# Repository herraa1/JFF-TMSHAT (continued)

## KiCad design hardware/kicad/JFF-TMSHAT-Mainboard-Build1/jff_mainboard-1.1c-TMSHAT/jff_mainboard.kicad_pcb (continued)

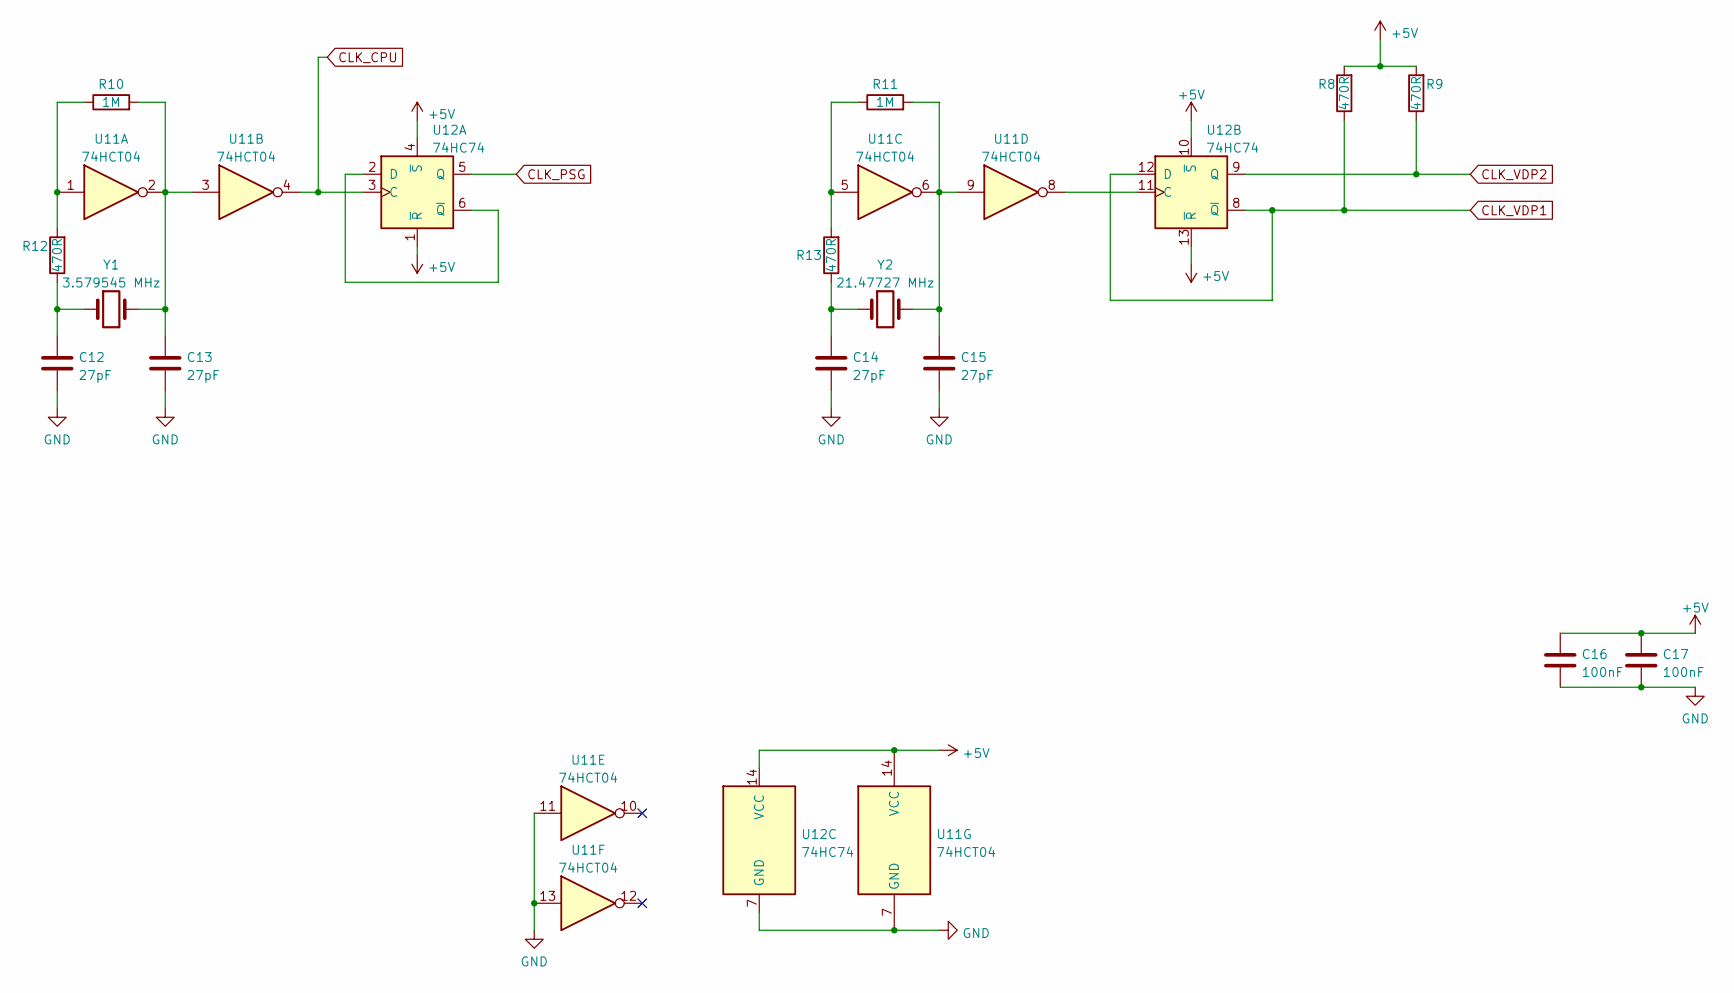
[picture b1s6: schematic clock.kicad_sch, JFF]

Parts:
C12, C13, C14, C15: 27pF; C_Disc_D3.0mm_W2.0mm_P2.50mm
C16, C17: 100nF; C_Disc_D3.0mm_W2.0mm_P2.50mm
R8, R9, R12, R13: 470R; R_Axial_DIN0204_L3.6mm_D1.6mm_P7.62mm_Horizontal
R10, R11: 1M; R_Axial_DIN0204_L3.6mm_D1.6mm_P7.62mm_Horizontal
U11: 74HCT04; DIP-14_W7.62mm_Socket
U12: 74HC74; DIP-14_W7.62mm_Socket
Y1: 3.579545 MHz; Crystal_HC49-U_Vertical
Y2: 21.47727 MHz; Crystal_HC49-U_Vertical

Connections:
+5V: C16.1, C17.1, R8.2, R9.2, U11.14 (VCC), U12.1 (~R), U12.4 (~S), U12.10 (~S), U12.13 (~R), U12.14 (VCC); also elsewhere on the board
CLK_CPU: U11.4, U12.3 (C); also elsewhere on the board
CLK_PSG: U12.5 (Q); also elsewhere on the board
CLK_VDP1: R8.1, U12.8 (~Q), U12.12 (D); also elsewhere on the board
CLK_VDP2: R9.1, U12.9 (Q); also elsewhere on the board
GND: C12.2, C13.2, C14.2, C15.2, C16.2, C17.2, U11.7 (GND), U11.11, U11.13, U12.7 (GND); also elsewhere on the board
unnamed: C12.1, R12.1, Y1.1
unnamed: C13.1, R10.2, U11.2, U11.3, Y1.2
unnamed: C14.1, R13.1, Y2.1
unnamed: C15.1, R11.2, U11.6, U11.9, Y2.2
unnamed: R10.1, R12.2, U11.1
unnamed: R11.1, R13.2, U11.5
unnamed: U12.2 (D), U12.6 (~Q)
unnamed: U11.8, U12.11 (C)

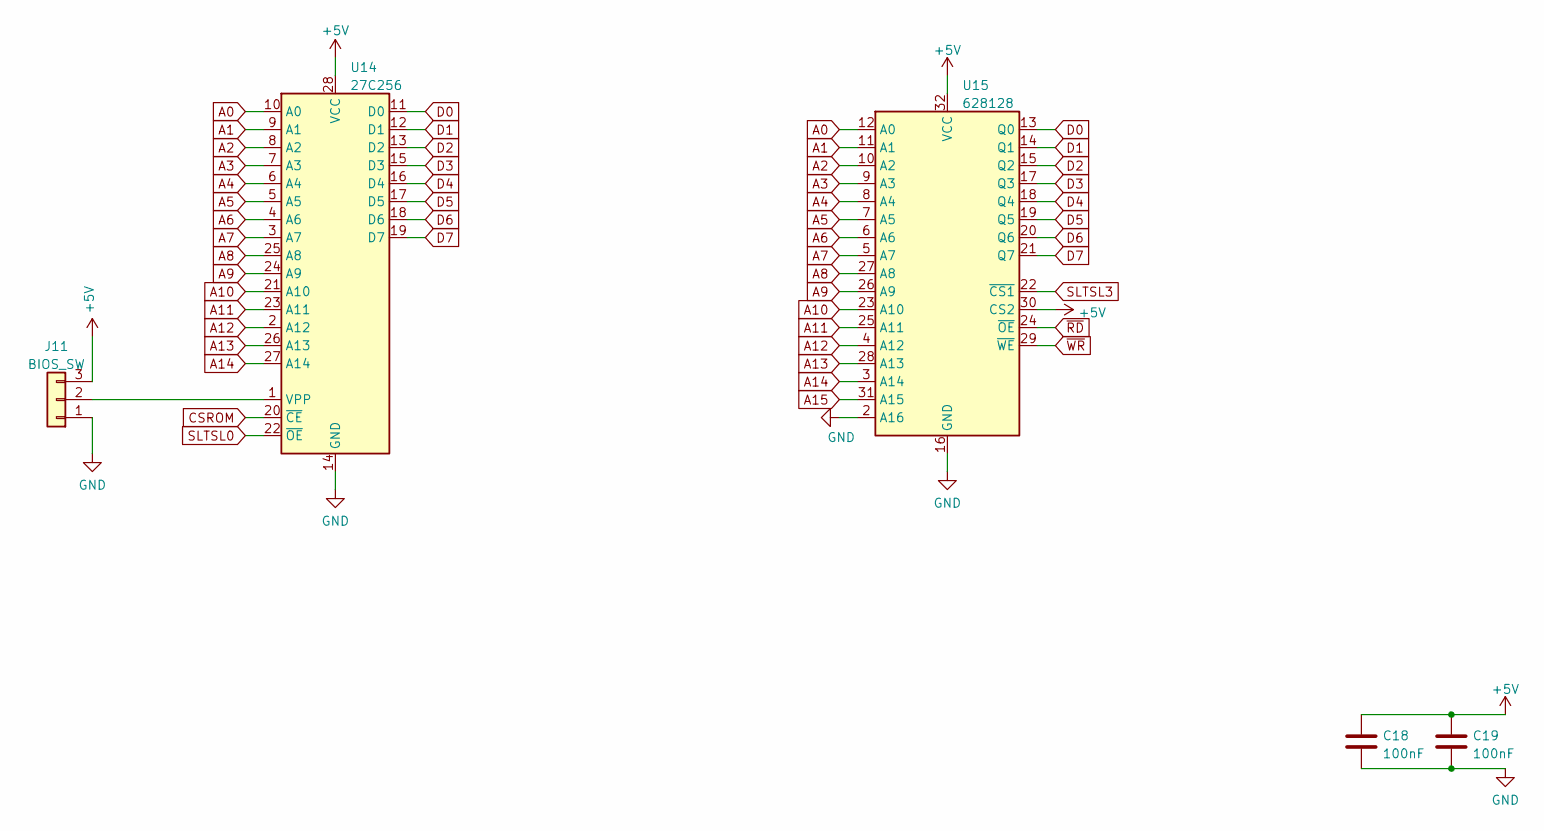
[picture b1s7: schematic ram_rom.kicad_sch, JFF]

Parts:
C18, C19: 100nF; C_Disc_D3.0mm_W2.0mm_P2.50mm
J11: BIOS_SW; PinHeader_1x03_P2.54mm_Vertical
U14: 27C256; DIP-28_W15.24mm_Socket
U15: 628128; DIP-32_W15.24mm_Socket

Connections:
+5V: C18.1, C19.1, J11.3, U14.28 (VCC), U15.30 (CS2), U15.32 (VCC); also elsewhere on the board
A0: U14.10 (A0), U15.12 (A0); also elsewhere on the board
A1: U14.9 (A1), U15.11 (A1); also elsewhere on the board
A2: U14.8 (A2), U15.10 (A2); also elsewhere on the board
A3: U14.7 (A3), U15.9 (A3); also elsewhere on the board
A4: U14.6 (A4), U15.8 (A4); also elsewhere on the board
A5: U14.5 (A5), U15.7 (A5); also elsewhere on the board
A6: U14.4 (A6), U15.6 (A6); also elsewhere on the board
A7: U14.3 (A7), U15.5 (A7); also elsewhere on the board
A8: U14.25 (A8), U15.27 (A8); also elsewhere on the board
A9: U14.24 (A9), U15.26 (A9); also elsewhere on the board
A10: U14.21 (A10), U15.23 (A10); also elsewhere on the board
A11: U14.23 (A11), U15.25 (A11); also elsewhere on the board
A12: U14.2 (A12), U15.4 (A12); also elsewhere on the board
A13: U14.26 (A13), U15.28 (A13); also elsewhere on the board
A14: U14.27 (A14), U15.3 (A14); also elsewhere on the board
A15: U15.31 (A15); also elsewhere on the board
CSROM: U14.20 (~CE); also elsewhere on the board
D0: U14.11 (D0), U15.13 (Q0); also elsewhere on the board
D1: U14.12 (D1), U15.14 (Q1); also elsewhere on the board
D2: U14.13 (D2), U15.15 (Q2); also elsewhere on the board
D3: U14.15 (D3), U15.17 (Q3); also elsewhere on the board
D4: U14.16 (D4), U15.18 (Q4); also elsewhere on the board
D5: U14.17 (D5), U15.19 (Q5); also elsewhere on the board
D6: U14.18 (D6), U15.20 (Q6); also elsewhere on the board
D7: U14.19 (D7), U15.21 (Q7); also elsewhere on the board
GND: C18.2, C19.2, J11.1, U14.14 (GND), U15.2 (A16), U15.16 (GND); also elsewhere on the board
unnamed: J11.2, U14.1 (VPP)
SLTSL0: U14.22 (~OE); also elsewhere on the board
SLTSL3: U15.22 (~CS1); also elsewhere on the board
~RD: U15.24 (~OE); also elsewhere on the board
~WR: U15.29 (~WE); also elsewhere on the board

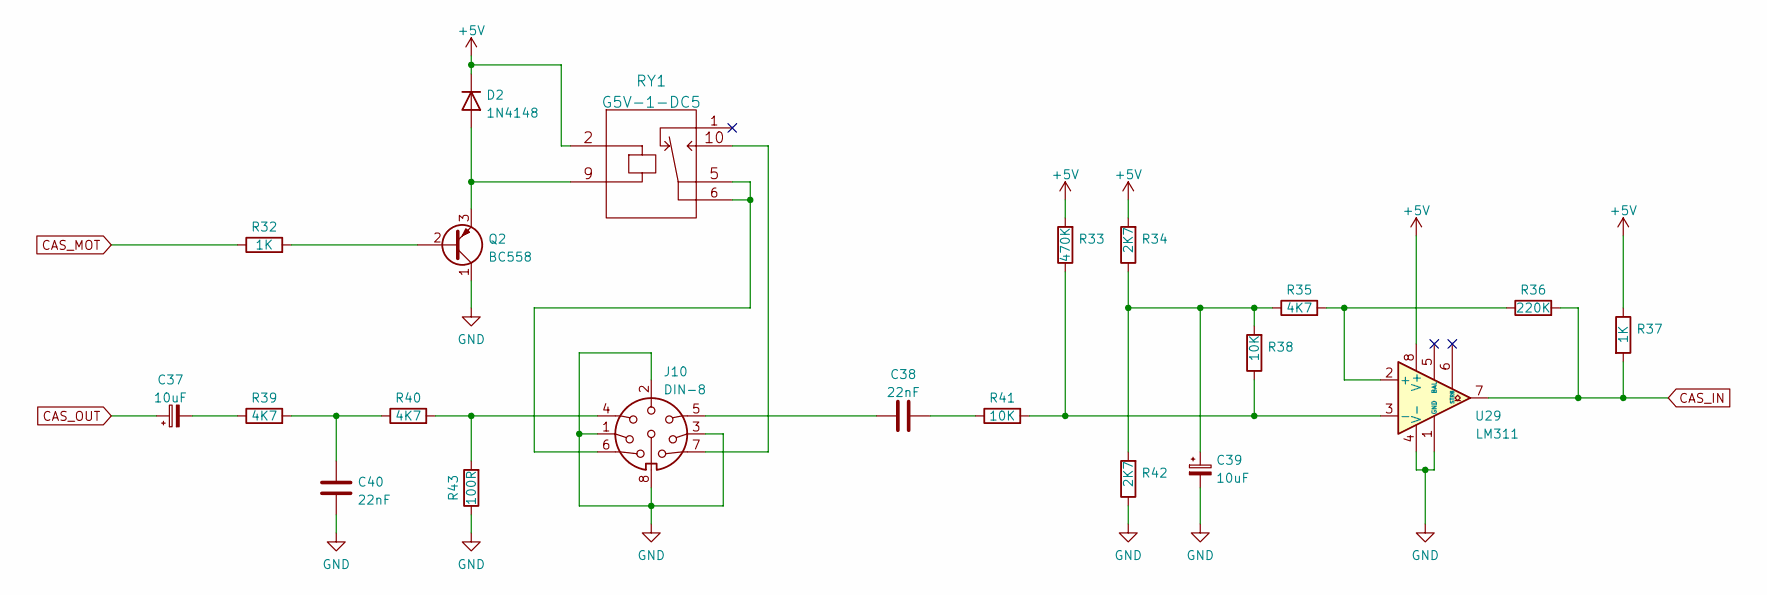
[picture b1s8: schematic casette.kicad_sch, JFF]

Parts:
C37, C39: 10uF; CP_Radial_D5.0mm_P2.50mm
C38, C40: 22nF; C_Disc_D3.0mm_W2.0mm_P2.50mm
D2: 1N4148; D_DO-35_SOD27_P7.62mm_Horizontal
J10: DIN-8; DIN8_eu
Q2: BC558; TO-92_Inline
R32, R37: 1K; R_Axial_DIN0204_L3.6mm_D1.6mm_P7.62mm_Horizontal
R33: 470K; R_Axial_DIN0204_L3.6mm_D1.6mm_P7.62mm_Horizontal
R34, R42: 2K7; R_Axial_DIN0204_L3.6mm_D1.6mm_P7.62mm_Horizontal
R35, R39, R40: 4K7; R_Axial_DIN0204_L3.6mm_D1.6mm_P7.62mm_Horizontal
R36: 220K; R_Axial_DIN0204_L3.6mm_D1.6mm_P7.62mm_Horizontal
R38, R41: 10K; R_Axial_DIN0204_L3.6mm_D1.6mm_P7.62mm_Horizontal
R43: 100R; R_Axial_DIN0204_L3.6mm_D1.6mm_P7.62mm_Horizontal
RY1: G5V-1-DC5; Relay_SPDT
U29: LM311; DIP-8_W7.62mm_Socket

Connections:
+5V: D2.1 (K), R33.2, R34.2, R37.1, RY1.2, U29.8 (V+); also elsewhere on the board
CAS_IN: R36.2, R37.2, U29.7; also elsewhere on the board
CAS_MOT: R32.1; also elsewhere on the board
CAS_OUT: C37.1; also elsewhere on the board
GND: C39.2, C40.1, J10.1, J10.2, J10.3, J10.8, Q2.1 (C), R42.1, R43.1, U29.1 (GND), U29.4 (V-); also elsewhere on the board
unnamed: C37.2, R39.1
unnamed: C38.1, J10.5
unnamed: C38.2, R41.1
unnamed: C39.1, R34.1, R35.1, R38.2, R42.2
unnamed: C40.2, R39.2, R40.1
unnamed: D2.2 (A), Q2.3 (E), RY1.9
unnamed: J10.4, R40.2, R43.2
unnamed: J10.6, RY1.5, RY1.6
unnamed: J10.7, RY1.10
unnamed: Q2.2 (B), R32.2
unnamed: R35.2, R36.1, U29.2 (+)
unnamed: R33.1, R38.1, R41.2, U29.3 (-)

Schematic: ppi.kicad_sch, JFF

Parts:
C29, C30, C31, C32, C33, C34, C35, C36: 100nF; C_Disc_D3.0mm_W2.0mm_P2.50mm
J9: KEYBOARD; PinHeader_2x08_P2.54mm_Vertical
R2: 10K; R_Axial_DIN0204_L3.6mm_D1.6mm_P7.62mm_Horizontal
RN1: 4.7K; R_Array_SIP9
U16: 74LS02; DIP-14_W7.62mm_Socket
U21: 74LS00; DIP-14_W7.62mm_Socket
U22: 74LS139; DIP-16_W7.62mm_Socket
U23: 74LS153; DIP-16_W7.62mm_Socket
U24: 74LS32; DIP-14_W7.62mm_Socket
U26: 82C55A; DIP-40_W15.24mm_Socket
U27: 74LS08; DIP-14_W7.62mm_Socket
U28: 74LS138; DIP-16_W7.62mm_Socket

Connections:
+5V: C29.1, C30.1, C31.1, C32.1, C33.1, C34.1, C35.1, C36.1, J9.2, R2.1, RN1.1 (common), U21.14 (VCC), U22.16 (VCC), U23.16 (VCC), U24.14 (VCC), U26.26 (VCC), U27.14 (VCC), U28.16 (VCC); also elsewhere on the board
A0: U26.9 (A0); also elsewhere on the board
A1: U26.8 (A1); also elsewhere on the board
A3: U28.1 (A0); also elsewhere on the board
A4: U28.2 (A1); also elsewhere on the board
A5: U28.3 (A2); also elsewhere on the board
A6: U28.5 (E2); also elsewhere on the board
A7: U28.6 (E3); also elsewhere on the board
A14: U22.14 (A0), U23.14 (S0); also elsewhere on the board
A15: U22.13 (A1), U23.2 (S1); also elsewhere on the board
BEEP: U26.10 (PC7); also elsewhere on the board
CAS_MOT: U26.13 (PC4); also elsewhere on the board
CAS_OUT: U26.12 (PC5); also elsewhere on the board
CS1: U24.6, U27.2, U27.4; also elsewhere on the board
CS2: U24.8, U27.5; also elsewhere on the board
CS12: U27.6; also elsewhere on the board
CSROM: U27.3; also elsewhere on the board
CS_PPI: U21.1, U26.6 (~CS), U28.10 (O5)
CS_PSG: U28.11 (O4); also elsewhere on the board
CS_VDP: U28.12 (O3); also elsewhere on the board
D0: U26.34 (D0); also elsewhere on the board
D1: U26.33 (D1); also elsewhere on the board
D2: U26.32 (D2); also elsewhere on the board
D3: U26.31 (D3); also elsewhere on the board
D4: U26.30 (D4); also elsewhere on the board
D5: U26.29 (D5); also elsewhere on the board
D6: U26.28 (D6); also elsewhere on the board
D7: U26.27 (D7); also elsewhere on the board
GND: C29.2, C30.2, C31.2, C32.2, C33.2, C34.2, C35.2, C36.2, J9.16, U16.9, U21.7 (GND), U21.9, U21.10, U21.12, U21.13, U22.8 (GND), U23.8 (GND), U24.7 (GND), U24.12, U24.13, U26.7 (GND), U27.7 (GND), U27.12, U27.13, U28.8 (GND); also elsewhere on the board
unnamed: U16.10, U24.2
unnamed: U21.3, U21.4
unnamed: U22.2 (A0), U23.7 (Za)
unnamed: U22.3 (A1), U23.9 (Zb)
unnamed: U22.1 (E), U24.3
unnamed: U22.12 (O0), U27.1
unnamed: U22.11 (O1), U24.5
unnamed: U22.10 (O2), U24.10
unnamed: U21.2, U21.6, U23.1 (Ea), U23.15 (Eb)
PA0: U23.6 (I0a), U26.4 (PA0)
PA1: U23.10 (I0b), U26.3 (PA1)
PA2: U23.5 (I1a), U26.2 (PA2)
PA3: U23.11 (I1b), U26.1 (PA3)
PA4: U23.4 (I2a), U26.40 (PA4)
PA5: U23.12 (I2b), U26.39 (PA5)
PA6: U23.3 (I3a), U26.38 (PA6)
PA7: U23.13 (I3b), U26.37 (PA7)
PB0: J9.1, RN1.2 (R1), U26.18 (PB0)
PB1: J9.3, RN1.3 (R2), U26.19 (PB1)
PB2: J9.5, RN1.4 (R3), U26.20 (PB2)
PB3: J9.7, RN1.5 (R4), U26.21 (PB3)
PB4: J9.9, RN1.6 (R5), U26.22 (PB4)
PB5: J9.11, RN1.7 (R6), U26.23 (PB5)
PB6: J9.13, RN1.8 (R7), U26.24 (PB6)
PB7: J9.15, RN1.9 (R8), U26.25 (PB7)
PC0: J9.4, U26.14 (PC0)
PC1: J9.6, U26.15 (PC1)
PC2: J9.8, U26.16 (PC2)
PC3: J9.10, U26.17 (PC3)
PC6: J9.12, U26.11 (PC6)
RESET: U26.35 (RESET); also elsewhere on the board
SLTSL0: U22.4 (O0); also elsewhere on the board
SLTSL1: U22.5 (O1); also elsewhere on the board
SLTSL2: U22.6 (O2); also elsewhere on the board
SLTSL3: U22.7 (O3); also elsewhere on the board
~INT: U27.8; also elsewhere on the board
~IORQ: U28.4 (E1); also elsewhere on the board
~MREQ: U24.1; also elsewhere on the board
~RD: U22.15 (E), U24.4, U24.9, U26.5 (~RD); also elsewhere on the board
~RESET: U21.5; also elsewhere on the board
~RFSH: U16.8; also elsewhere on the board
~SLT_INT: R2.2, U27.10; also elsewhere on the board
~VDP_INT: U27.9; also elsewhere on the board
~WR: U26.36 (~WR); also elsewhere on the board

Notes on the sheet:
IO90 - PRINTER (NOT USED) IO98 - VDP IOA0 - PSG IOA8 - PPI

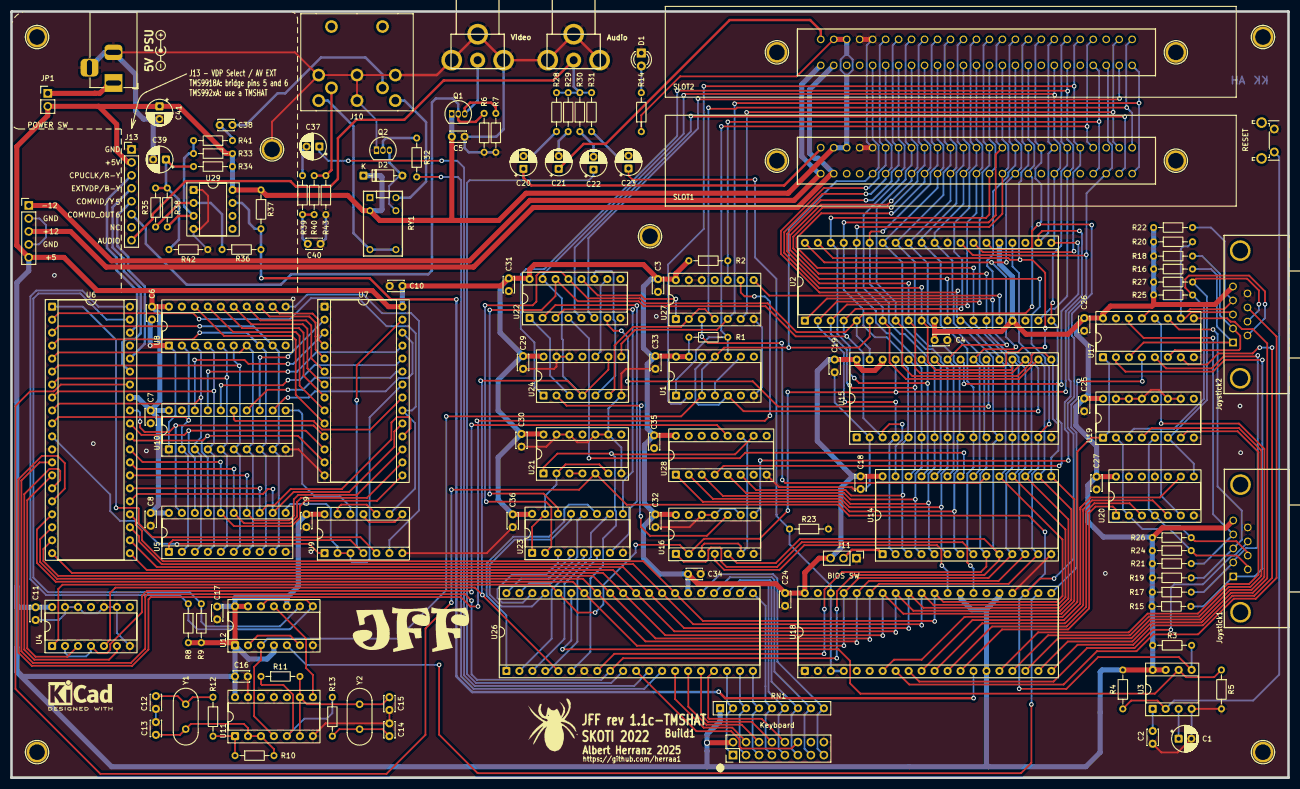
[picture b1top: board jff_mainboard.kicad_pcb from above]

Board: 2 copper layers, 250.0 x 150.0 mm, 144 parts (0 on the bottom side), 198 nets.

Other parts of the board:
G01: LOGO; jff_logo_25x10
G02: LOGO; spider_logo_small_neg
MH01, MH02, MH03, MH04, MH05, MH06, MH07, MH08, MH09, MH10: VAL*; Hole_3mm

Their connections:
GND: MH01.1, MH02.1, MH03.1, MH04.1, MH05.1, MH06.1, MH07.1, MH08.1, MH09.1, MH10.1; also elsewhere on the board

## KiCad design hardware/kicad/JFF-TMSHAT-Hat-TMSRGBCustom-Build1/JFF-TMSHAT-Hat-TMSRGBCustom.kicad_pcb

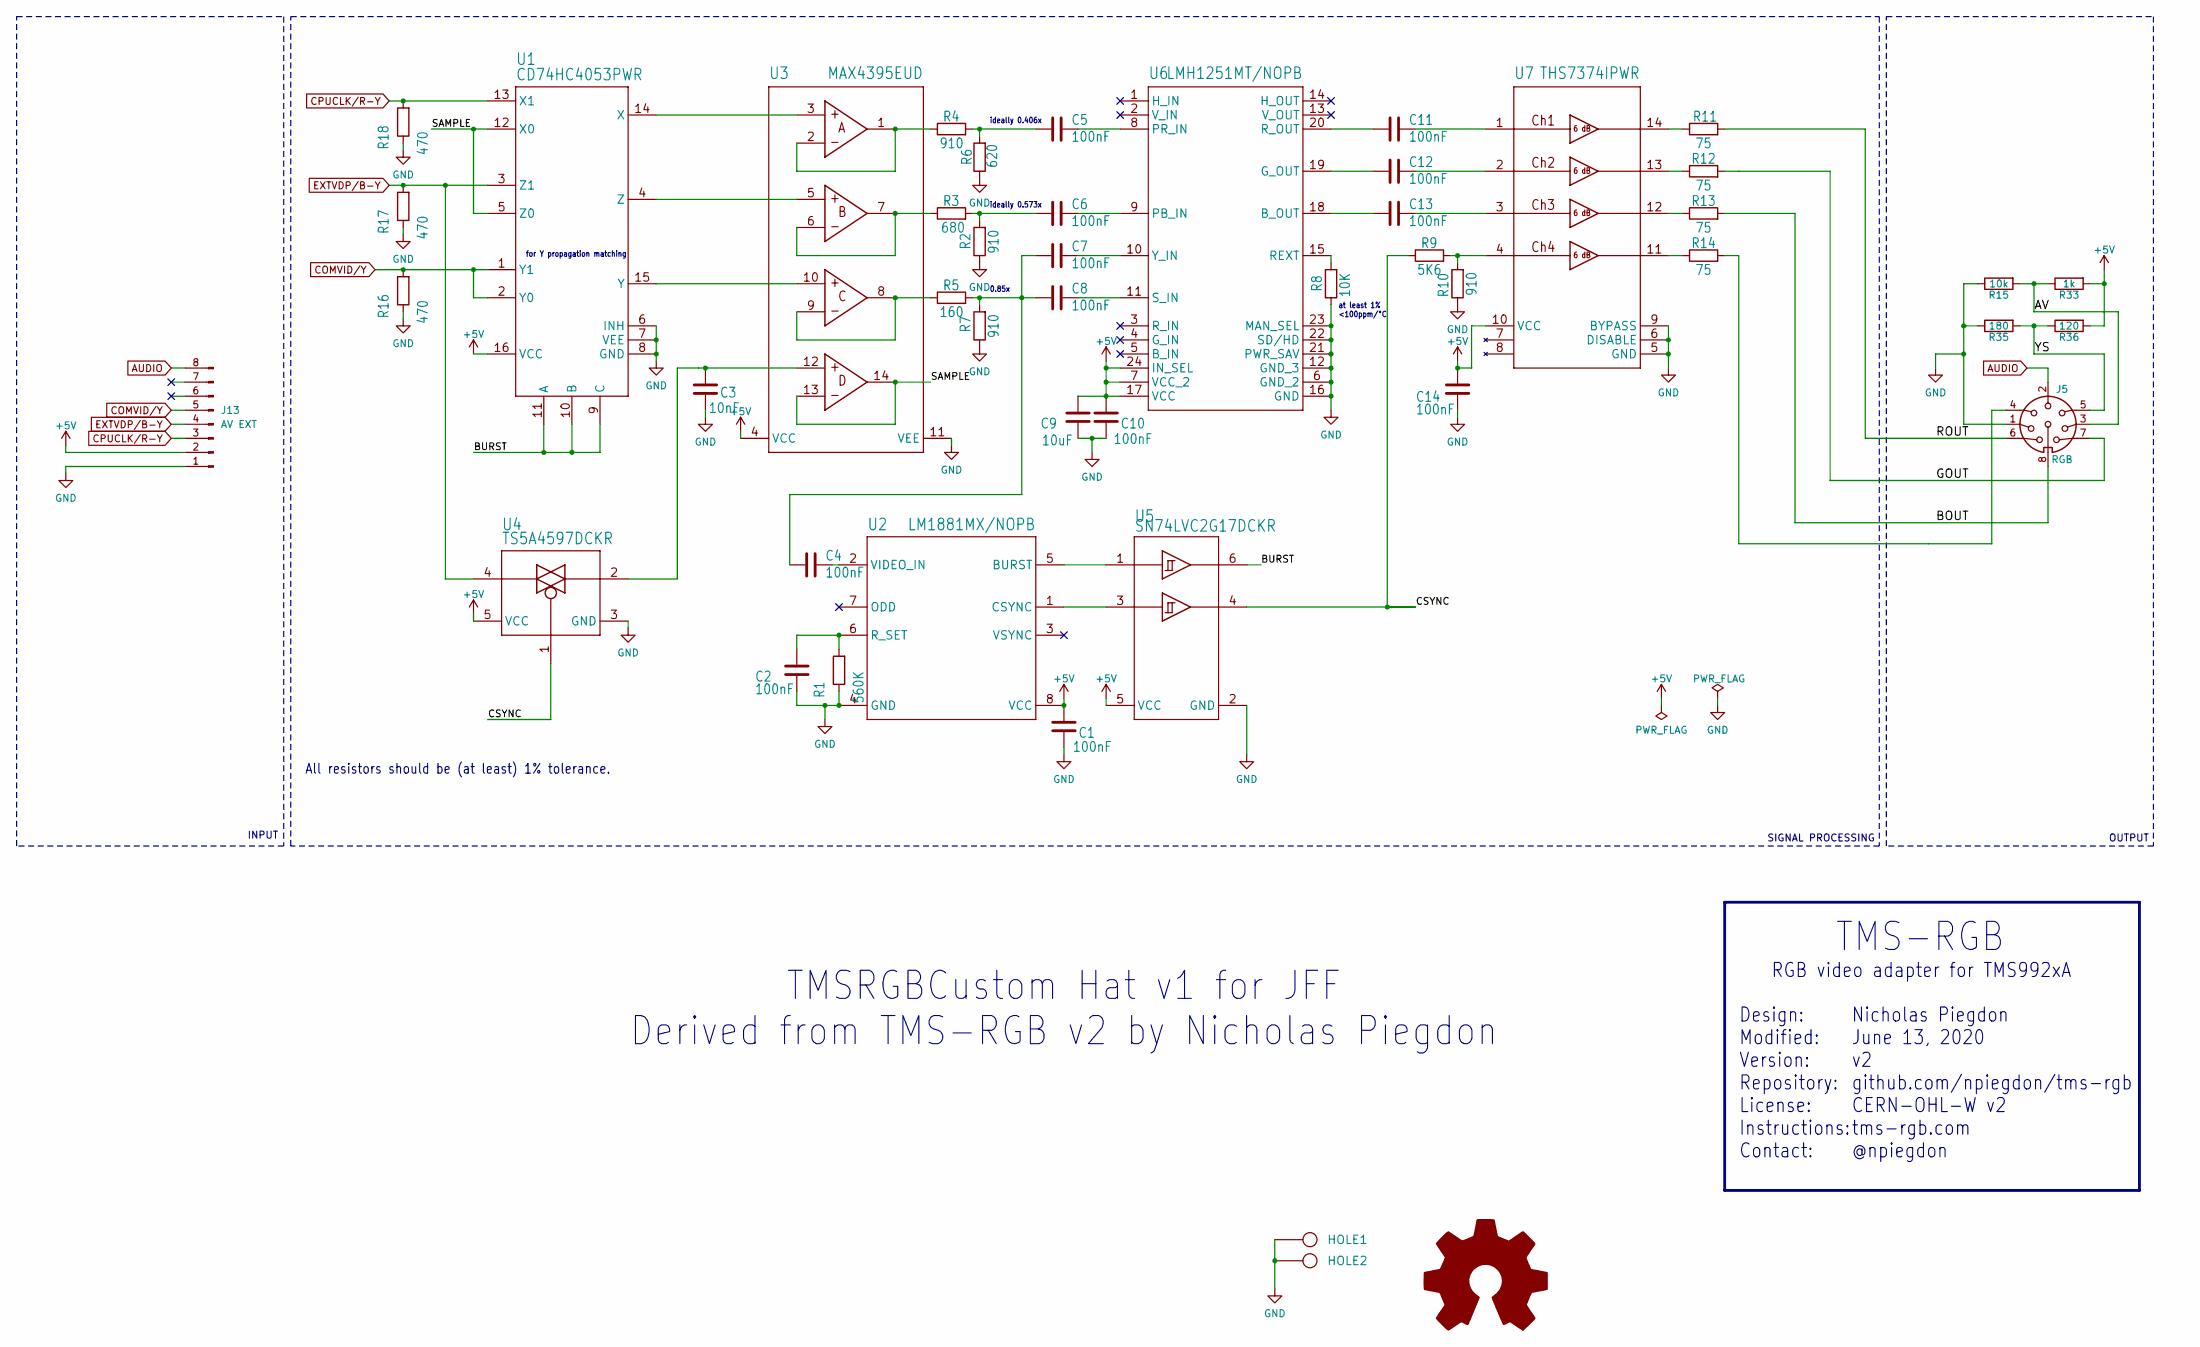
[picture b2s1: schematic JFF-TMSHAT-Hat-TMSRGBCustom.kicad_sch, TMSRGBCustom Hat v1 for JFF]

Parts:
C1, C2, C4, C5, C6, C7, C8, C10, C11, C12, C13, C14: 100nF; C_0805_2012Metric_Pad1.18x1.45mm_HandSolder
C3: 10nF; C_0805_2012Metric_Pad1.18x1.45mm_HandSolder
C9: 10uF; C_1206_3216Metric_Pad1.33x1.80mm_HandSolder
HOLE1, HOLE2: HOLE; Hole_3mm
J5: RGB; DIN8_eu
J13: AV EXT; PinSocket_1x08_P2.54mm_Vertical
R1: 560K; R_0805_2012Metric_Pad1.20x1.40mm_HandSolder
R2, R4, R7, R10: 910; R_0805_2012Metric_Pad1.20x1.40mm_HandSolder
R3: 680; R_0805_2012Metric_Pad1.20x1.40mm_HandSolder
R5: 160; R_0805_2012Metric_Pad1.20x1.40mm_HandSolder
R6: 620; R_0805_2012Metric_Pad1.20x1.40mm_HandSolder
R8: 10K; R_0805_2012Metric_Pad1.20x1.40mm_HandSolder
R9: 5K6; R_0805_2012Metric_Pad1.20x1.40mm_HandSolder
R11, R12, R13, R14: 75; R_0805_2012Metric_Pad1.20x1.40mm_HandSolder
R15: 10k; R_0805_2012Metric_Pad1.20x1.40mm_HandSolder
R16, R17, R18: 470; R_0805_2012Metric_Pad1.20x1.40mm_HandSolder
R33: 1k; R_0805_2012Metric_Pad1.20x1.40mm_HandSolder
R35: 180; R_0805_2012Metric_Pad1.20x1.40mm_HandSolder
R36: 120; R_0805_2012Metric_Pad1.20x1.40mm_HandSolder
SYM1: Logo_Open_Hardware_Large; OSHW-Logo_7.5x8mm_SilkScreen
U1: CD74HC4053PWR; TSSOP-16_4.4x5mm_P0.65mm
U2: LM1881MX/NOPB; SOIC-8_3.9x4.9mm_P1.27mm
U3: MAX4395EUD; TSSOP-14_4.4x5mm_P0.65mm
U4: TS5A4597DCKR; SOT-353_SC-70-5_Handsoldering
U5: SN74LVC2G17DCKR; SOT-363_SC-70-6_Handsoldering
U6: LMH1251MT/NOPB; TSSOP-24_4.4x7.8mm_P0.65mm
U7: THS7374IPWR; TSSOP-14_4.4x5mm_P0.65mm

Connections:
+5V: C1.1, C9.1, C10.1, C14.1, J13.2, R33.2, R36.2, U1.16 (VCC), U2.8 (VCC), U3.4 (VCC), U4.5 (VCC), U5.5 (VCC), U6.7 (VCC_2), U6.17 (VCC), U6.24 (IN_SEL), U7.10 (VCC)
/AV: J5.3, R15.2, R33.1
/BOUT: J5.8, R13.2
/BURST: U1.9 (C), U1.10 (B), U1.11 (A), U5.6 (1Y)
/CSYNC: R9.1, U4.1 (IN), U5.4 (2Y)
/GOUT: J5.7, R12.2
/ROUT: J5.6, R11.2
/SAMPLE: U1.5 (Z0), U1.12 (X0), U3.13 (D-), U3.14 (D)
/YS: J5.5, R35.2, R36.1
AUDIO: J5.2, J13.8
COMVID/Y: J13.5, R16.2, U1.1 (Y1), U1.2 (Y0)
CPUCLK/R-Y: J13.3, R18.2, U1.13 (X1)
EXTVDP/B-Y: J13.4, R17.2, U1.3 (Z1), U4.4 (NC)
GND: C1.2, C2.2, C3.2, C9.2, C10.2, C14.2, HOLE1.1, HOLE2.1, J5.1, J13.1, R1.1, R2.1, R6.1, R7.1, R8.1, R10.1, R15.1, R16.1, R17.1, R18.1, R35.1, U1.6 (INH), U1.7 (VEE), U1.8 (GND), U2.4 (GND), U3.11 (VEE), U4.3 (GND), U5.2 (GND), U6.6 (GND_2), U6.12 (GND_3), U6.16 (GND), U6.21 (PWR_SAV), U6.22 (SD/HD), U6.23 (MAN_SEL), U7.5 (GND), U7.6 (DISABLE), U7.9 (BYPASS)
unnamed: C4.1, C7.1, C8.1, R5.2, R7.2
unnamed: C5.1, R4.2, R6.2
unnamed: C6.1, R2.2, R3.2
unnamed: J5.4, R14.2
unnamed: U1.14 (X), U3.3 (A+)
unnamed: U1.15 (Y), U3.10 (C+)
unnamed: U1.4 (Z), U3.5 (B+)
unnamed: U2.5 (BURST), U5.1 (1A)
unnamed: U2.1 (CSYNC), U5.3 (2A)
unnamed: C2.1, R1.2, U2.6 (R_SET)
unnamed: C4.2, U2.2 (VIDEO_IN)
unnamed: R4.1, U3.1 (A), U3.2 (A-)
unnamed: R3.1, U3.6 (B-), U3.7 (B)
unnamed: R5.1, U3.8 (C), U3.9 (C-)
unnamed: C3.1, U3.12 (D+), U4.2 (COM)
unnamed: C13.1, U6.18 (B_OUT)
unnamed: C12.1, U6.19 (G_OUT)
unnamed: C6.2, U6.9 (PB_IN)
unnamed: C5.2, U6.8 (PR_IN)
unnamed: R8.2, U6.15 (REXT)
unnamed: C11.1, U6.20 (R_OUT)
unnamed: C8.2, U6.11 (S_IN)
unnamed: C7.2, U6.10 (Y_IN)
unnamed: C11.2, U7.1 (CH1IN)
unnamed: R11.1, U7.14 (CH1OUT)
unnamed: C12.2, U7.2 (CH2IN)
unnamed: R12.1, U7.13 (CH2OUT)
unnamed: C13.2, U7.3 (CH3IN)
unnamed: R13.1, U7.12 (CH3OUT)
unnamed: R9.2, R10.2, U7.4 (CH4IN)
unnamed: R14.1, U7.11 (CH4OUT)

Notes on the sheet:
for Y propagation matching
${TITLE} Derived from TMS-RGB v2 by Nicholas Piegdon
OUTPUT
at least 1% <100ppm/°C
TMS-RGB
ideally 0.573x
SIGNAL PROCESSING
Nicholas Piegdon June 13, 2020 v2 github.com/npiegdon/tms-rgb CERN-OHL-W v2 tms-rgb.com @npiegdon
All resistors should be (at least) 1% tolerance.
RGB video adapter for TMS992xA
Design: Modified: Version: Repository: License: Instructions: Contact:
0.85x
ideally 0.406x
INPUT

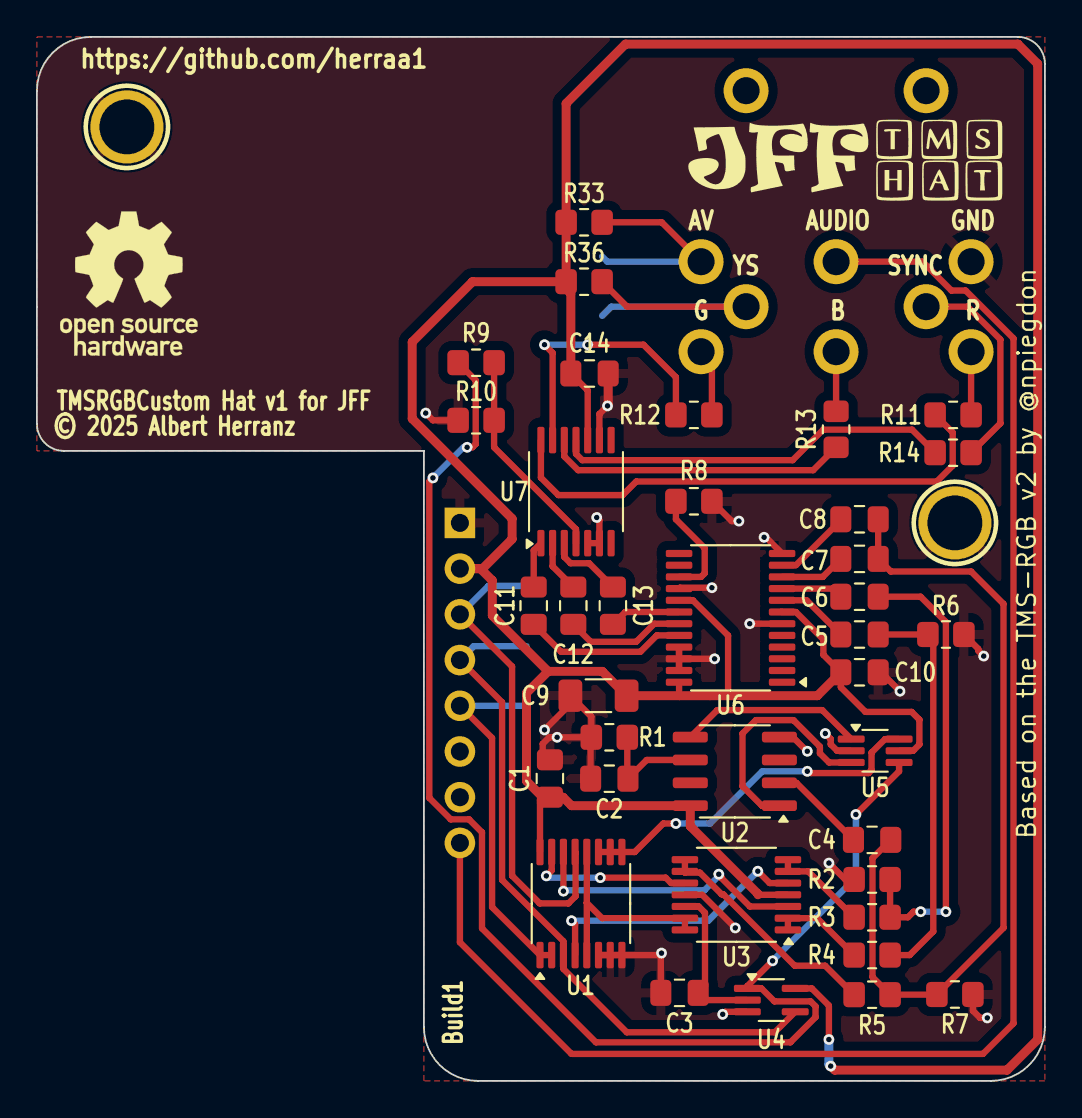
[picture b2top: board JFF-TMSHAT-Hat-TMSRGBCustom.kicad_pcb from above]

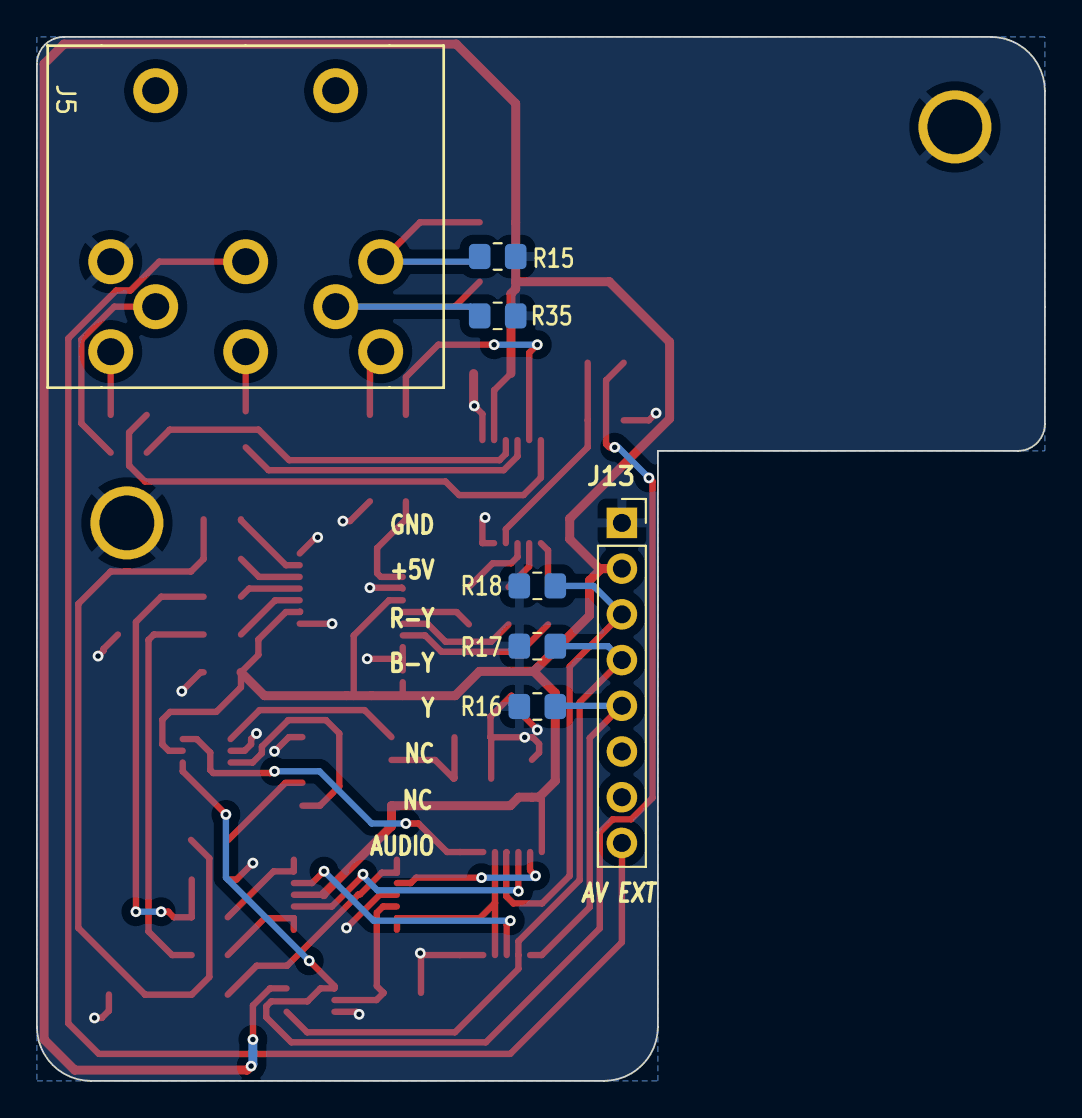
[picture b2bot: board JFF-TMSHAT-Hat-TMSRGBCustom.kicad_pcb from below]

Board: 2 copper layers, 56.0 x 58.0 mm, 47 parts (7 on the bottom side), 45 nets.

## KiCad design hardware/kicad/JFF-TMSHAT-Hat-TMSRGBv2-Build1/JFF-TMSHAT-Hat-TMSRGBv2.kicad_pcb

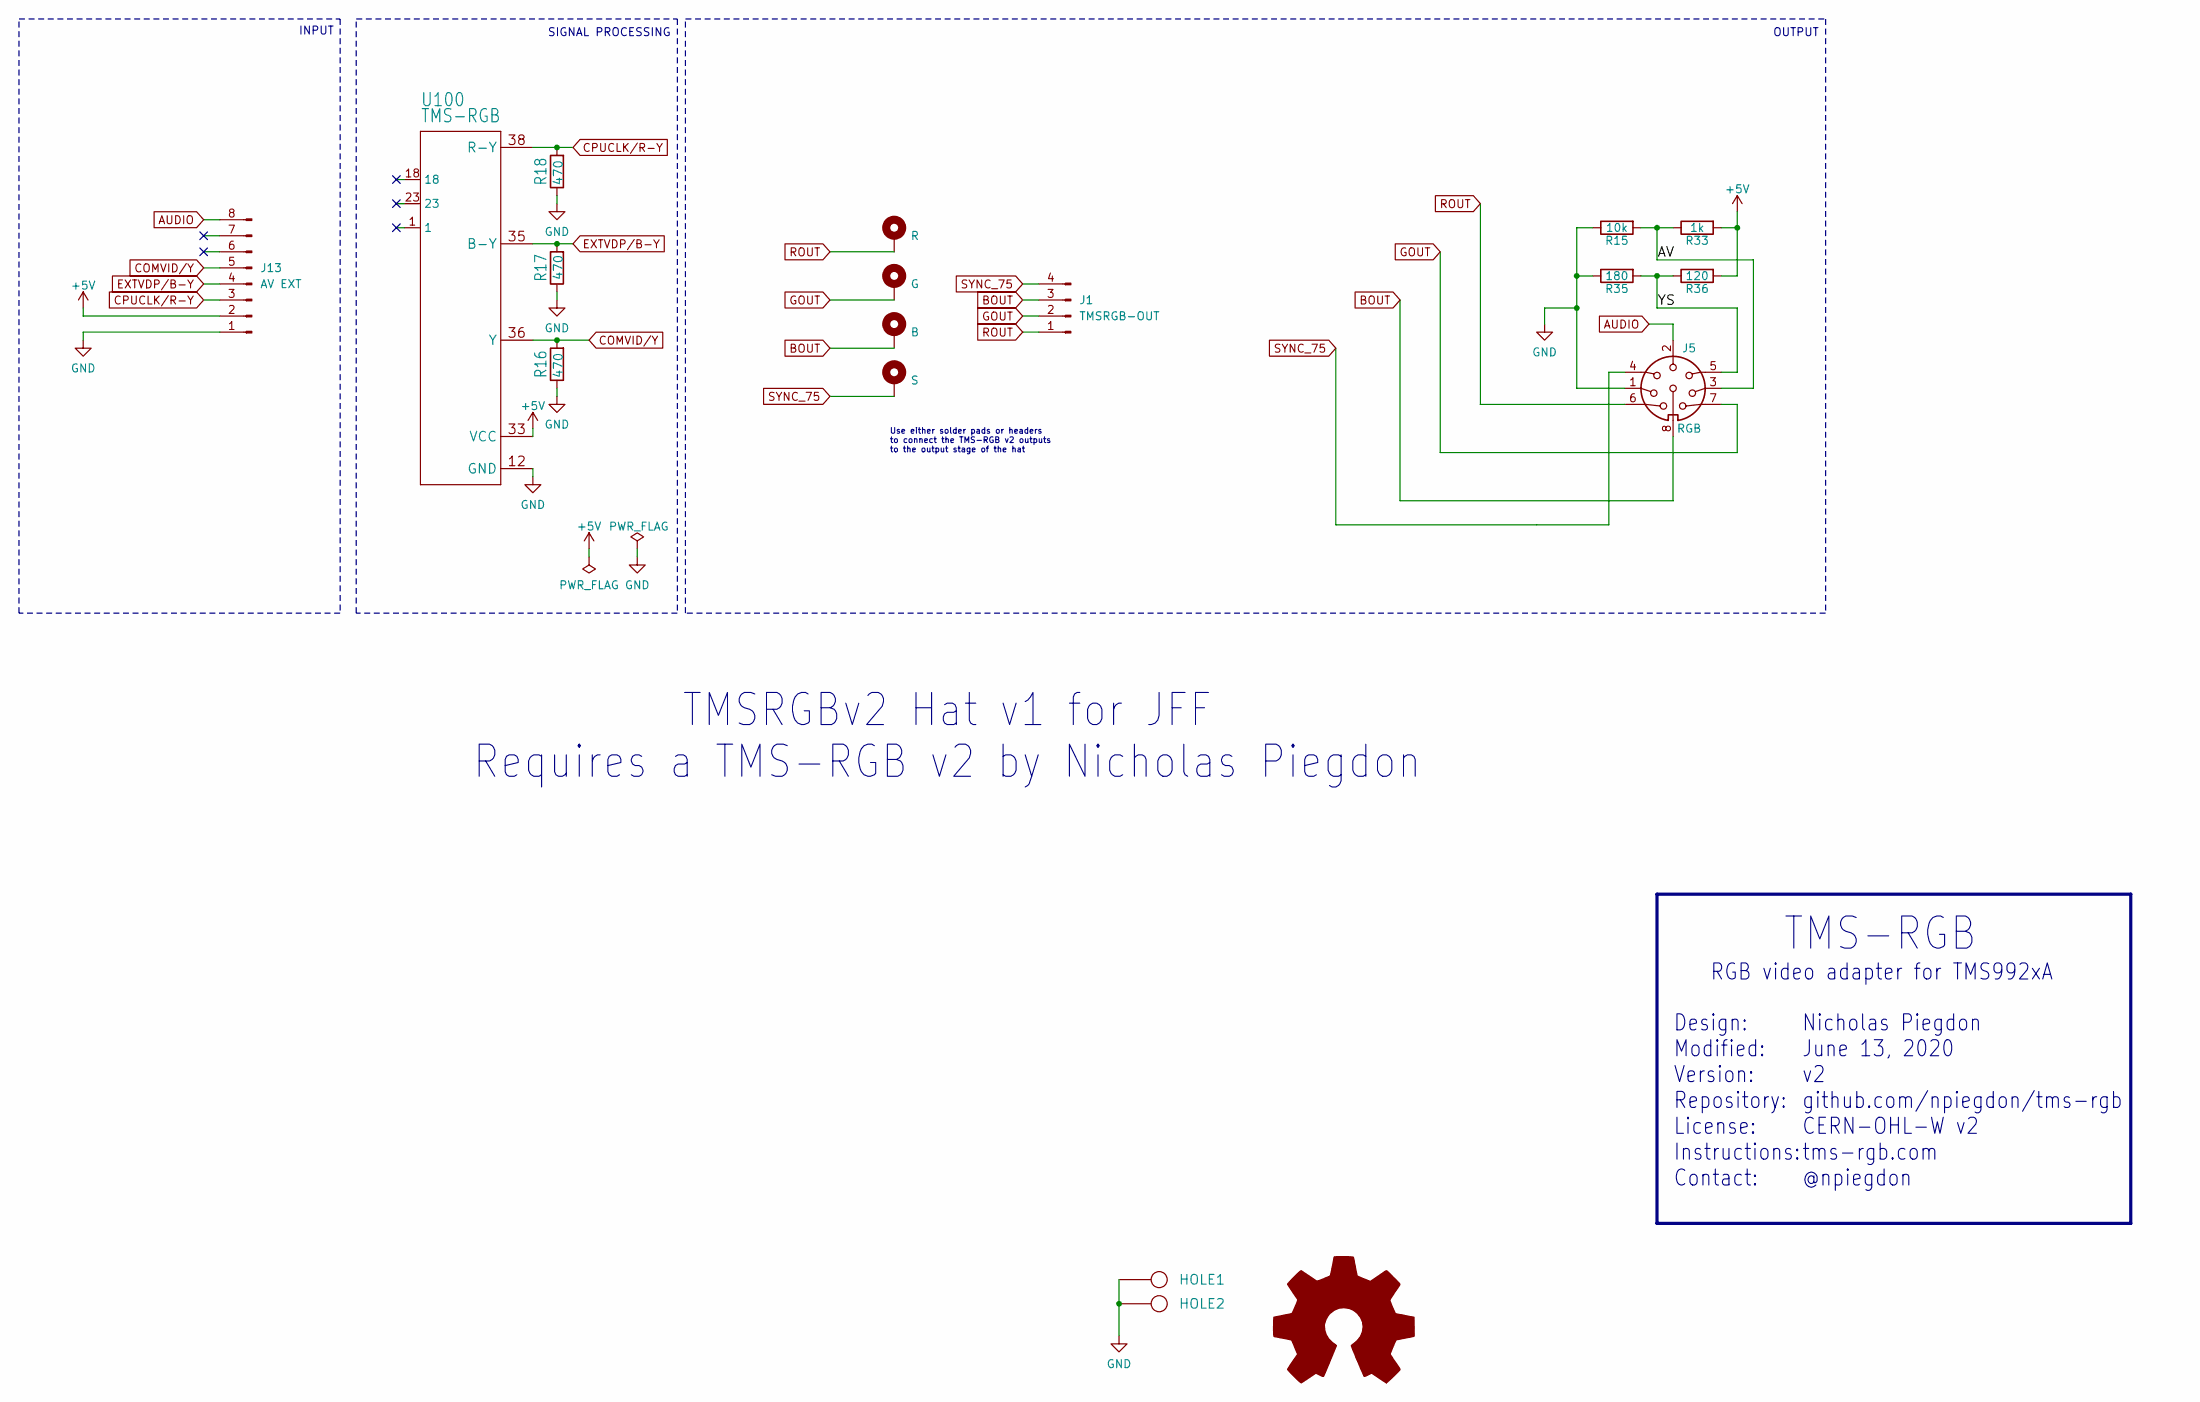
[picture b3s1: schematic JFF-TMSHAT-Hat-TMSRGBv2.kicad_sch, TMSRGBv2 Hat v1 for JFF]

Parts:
H1: R; TestPoint_Pad_3.0x3.0mm
H2: G; TestPoint_Pad_3.0x3.0mm
H3: B; TestPoint_Pad_3.0x3.0mm
H4: S; TestPoint_Pad_3.0x3.0mm
HOLE1, HOLE2: HOLE; Hole_3mm
J1: TMSRGB-OUT; JST_XH_B4B-XH-A_1x04_P2.50mm_Vertical
J5: RGB; DIN8_eu
J13: AV EXT; PinSocket_1x08_P2.54mm_Vertical
R15: 10k; R_0805_2012Metric_Pad1.20x1.40mm_HandSolder
R16, R17, R18: 470; R_0805_2012Metric_Pad1.20x1.40mm_HandSolder
R33: 1k; R_0805_2012Metric_Pad1.20x1.40mm_HandSolder
R35: 180; R_0805_2012Metric_Pad1.20x1.40mm_HandSolder
R36: 120; R_0805_2012Metric_Pad1.20x1.40mm_HandSolder
SYM1: Logo_Open_Hardware_Large; OSHW-Logo_7.5x8mm_SilkScreen
U100: TMS-RGB; TMS992XA

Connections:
+5V: J13.2, R33.2, R36.2, U100.33 (VCC)
/AV: J5.3, R15.2, R33.1
/YS: J5.5, R35.2, R36.1
AUDIO: J5.2, J13.8
BOUT: H3.1, J1.3, J5.8
COMVID/Y: J13.5, R16.2, U100.36 (Y)
CPUCLK/R-Y: J13.3, R18.2, U100.38 (R-Y)
EXTVDP/B-Y: J13.4, R17.2, U100.35 (B-Y)
GND: HOLE1.1, HOLE2.1, J5.1, J13.1, R15.1, R16.1, R17.1, R18.1, R35.1, U100.12 (GND)
GOUT: H2.1, J1.2, J5.7
ROUT: H1.1, J1.1, J5.6
SYNC_75: H4.1, J1.4, J5.4

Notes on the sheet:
TMS-RGB
${TITLE} Requires a TMS-RGB v2 by Nicholas Piegdon
RGB video adapter for TMS992xA
Use either solder pads or headers to connect the TMS-RGB v2 outputs to the output stage of the hat
Design: Modified: Version: Repository: License: Instructions: Contact:
SIGNAL PROCESSING
OUTPUT
Nicholas Piegdon June 13, 2020 v2 github.com/npiegdon/tms-rgb CERN-OHL-W v2 tms-rgb.com @npiegdon
INPUT
